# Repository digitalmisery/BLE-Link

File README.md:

BLE-Link
========

Bluetooth Low-Energy Serial Interface

The board files are shared on OSH Park:
[BLE Link](http://oshpark.com/shared_projects/47GbNjng)
[Tag-Connect Adapter](http://oshpark.com/shared_projects/hpRTwmXp)

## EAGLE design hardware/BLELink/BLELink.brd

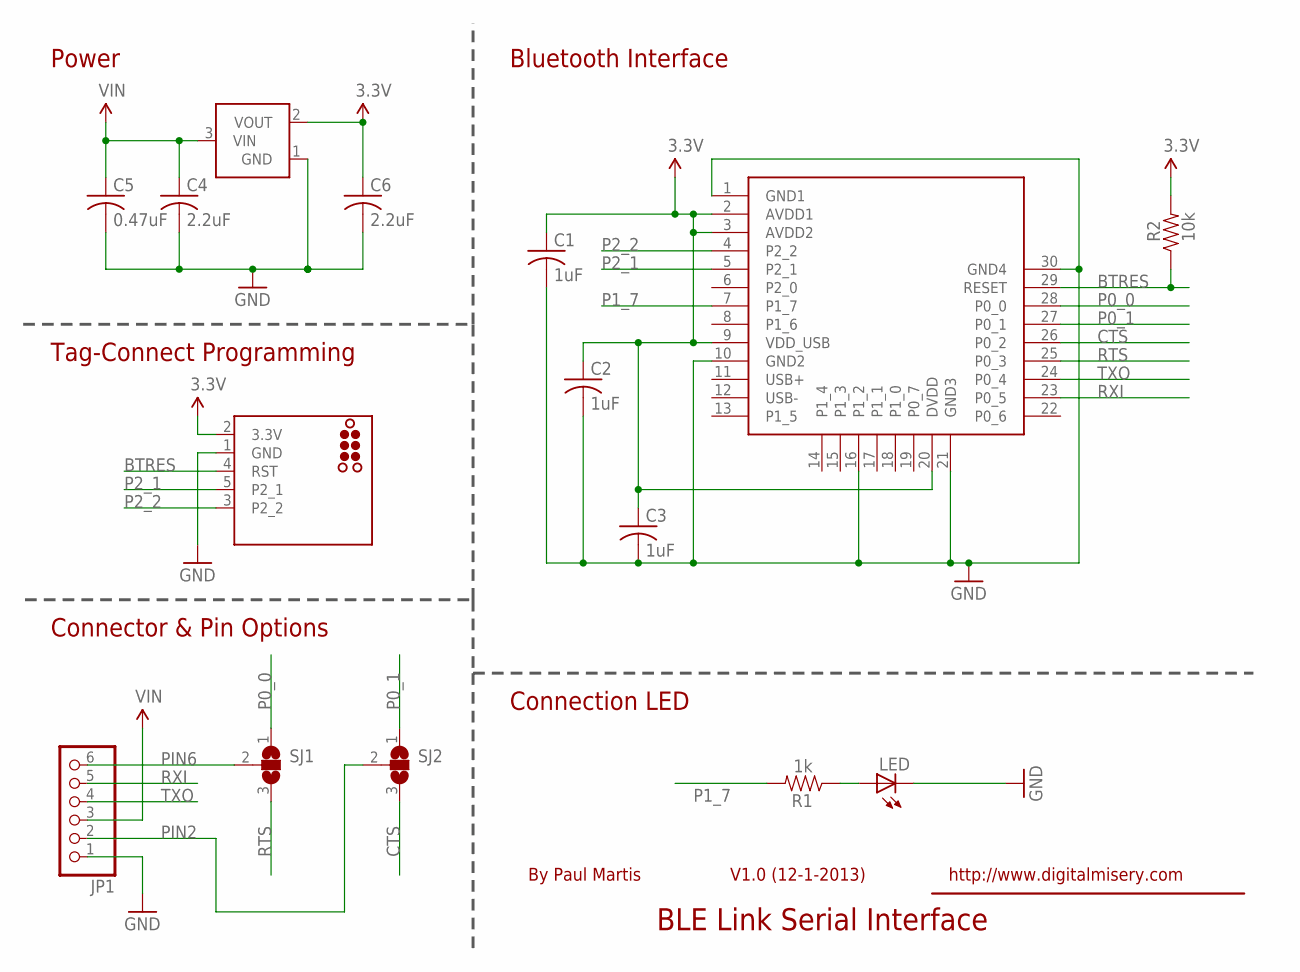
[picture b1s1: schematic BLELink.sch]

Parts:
C1, C2, C3: 1uF; C0805K
C4, C6: 2.2uF; C0805K
C5: 0.47uF; C0805K
J1: TC2030-CC-DEBUGGER; TC2030-MCP-NL
JP1: PINHD-1X6CB; 1X06-CLEANBIG
LED: LEDCHIP-LED0805; CHIP-LED0805
R1: 1k; 0805
R2: 10k; 0805
SJ1, SJ2: SJ2W; SJ_2
U1: MCP1700; SOT23-3
U2: BLE112-A

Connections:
3.3V: C1.1, C2.1, C3.1, C6.1, J1.2 (3.3V), R2.2, U1.2 (VOUT), U2.2 (AVDD1), U2.3 (AVDD2), U2.9 (VDD_USB), U2.20 (DVDD)
BTRES: J1.4 (RST), R2.1, U2.29 (RESET)
CTS: SJ2.3, U2.26 (P0_2)
GND: C1.2, C2.2, C3.2, C4.2, C5.2, C6.2, J1.1 (GND), JP1.1, LED.C, U1.1 (GND), U2.1 (GND1), U2.10 (GND2), U2.16 (P1_2), U2.21 (GND3), U2.30 (GND4)
unnamed: LED.A, R1.1
P0_0: SJ1.1, U2.28 (P0_0)
P0_1: SJ2.1, U2.27 (P0_1)
P1_7: R1.2, U2.7 (P1_7)
P2_1: J1.5 (P2_1), U2.5 (P2_1)
P2_2: J1.3 (P2_2), U2.4 (P2_2)
PIN2: JP1.2, SJ2.2
PIN6: JP1.6, SJ1.2
RTS: SJ1.3, U2.25 (P0_3)
RXI: JP1.5, U2.23 (P0_5)
TXO: JP1.4, U2.24 (P0_4)
VIN: C4.1, C5.1, JP1.3, U1.3 (VIN)

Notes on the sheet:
BLE Link Serial Interface
V1.0 (12-1-2013)
By Paul Martis
http://www.digitalmisery.com
Power
Bluetooth Interface
Connector & Pin Options
Tag-Connect Programming
Connection LED

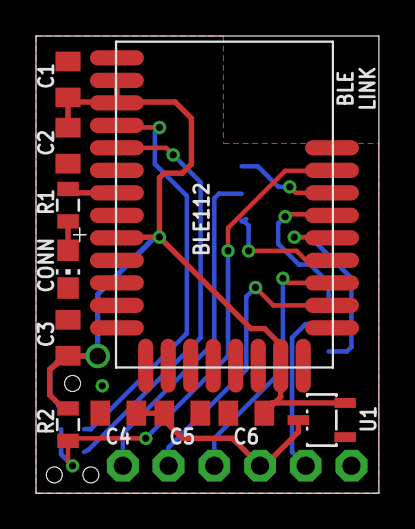
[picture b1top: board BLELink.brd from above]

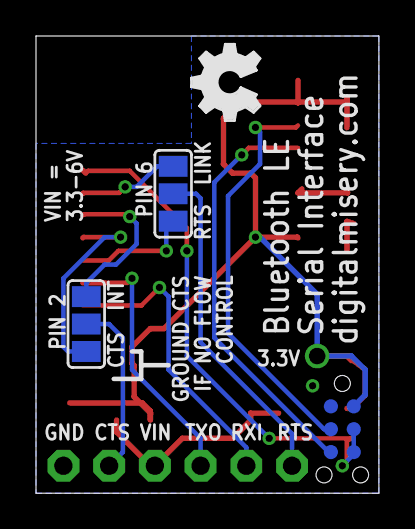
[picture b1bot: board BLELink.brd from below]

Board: 2 copper layers, 19.1 x 25.4 mm, 16 parts (4 on the bottom side), 16 nets.

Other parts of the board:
U$1: OSHW_FILLX150_NOTEXT

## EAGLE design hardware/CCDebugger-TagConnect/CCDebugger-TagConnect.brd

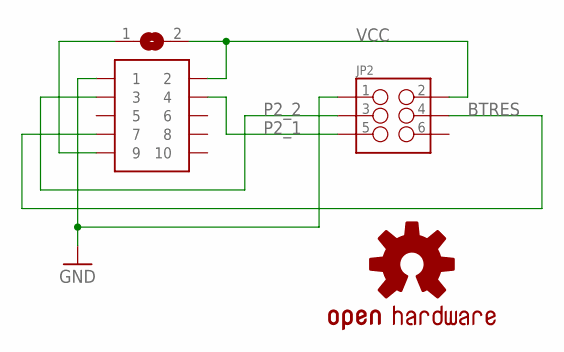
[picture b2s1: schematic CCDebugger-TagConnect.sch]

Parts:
JP2: M03X2; 2X3-SHROUDED
LOGO1: OSHW-LOGOS; OSHW-LOGO-S
VCC: SJ
X1: CONN_5-2-FTSH-V; FTSH-105-DV

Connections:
BTRES: JP2.4, X1.7
GND: JP2.1, X1.1
unnamed: VCC.1, X1.9
P2_1: JP2.5, X1.4
P2_2: JP2.3, X1.3
VCC: JP2.2, VCC.2, X1.2

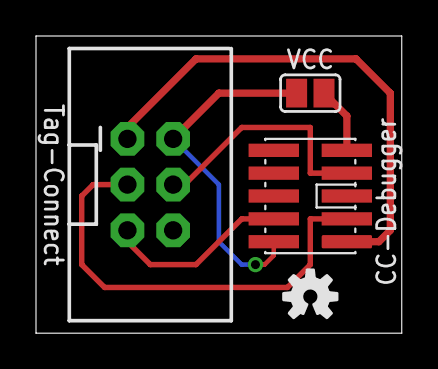
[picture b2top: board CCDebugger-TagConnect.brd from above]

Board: 2 copper layers, 20.3 x 16.5 mm, 4 parts (0 on the bottom side), 6 nets.

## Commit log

2014-01-12 Re-sized images
2014-01-12 Added links to OSH Park.

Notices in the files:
parts and their libraries:
SparkFun-RF: Licensing: CC v3.0 Share-Alike You are welcome to use this library for commercial purposes.
Tag-Connect: ©2009 ROFA.cz - modified and updated by Robert Darlington ‹rdarlington@gmail.com›
